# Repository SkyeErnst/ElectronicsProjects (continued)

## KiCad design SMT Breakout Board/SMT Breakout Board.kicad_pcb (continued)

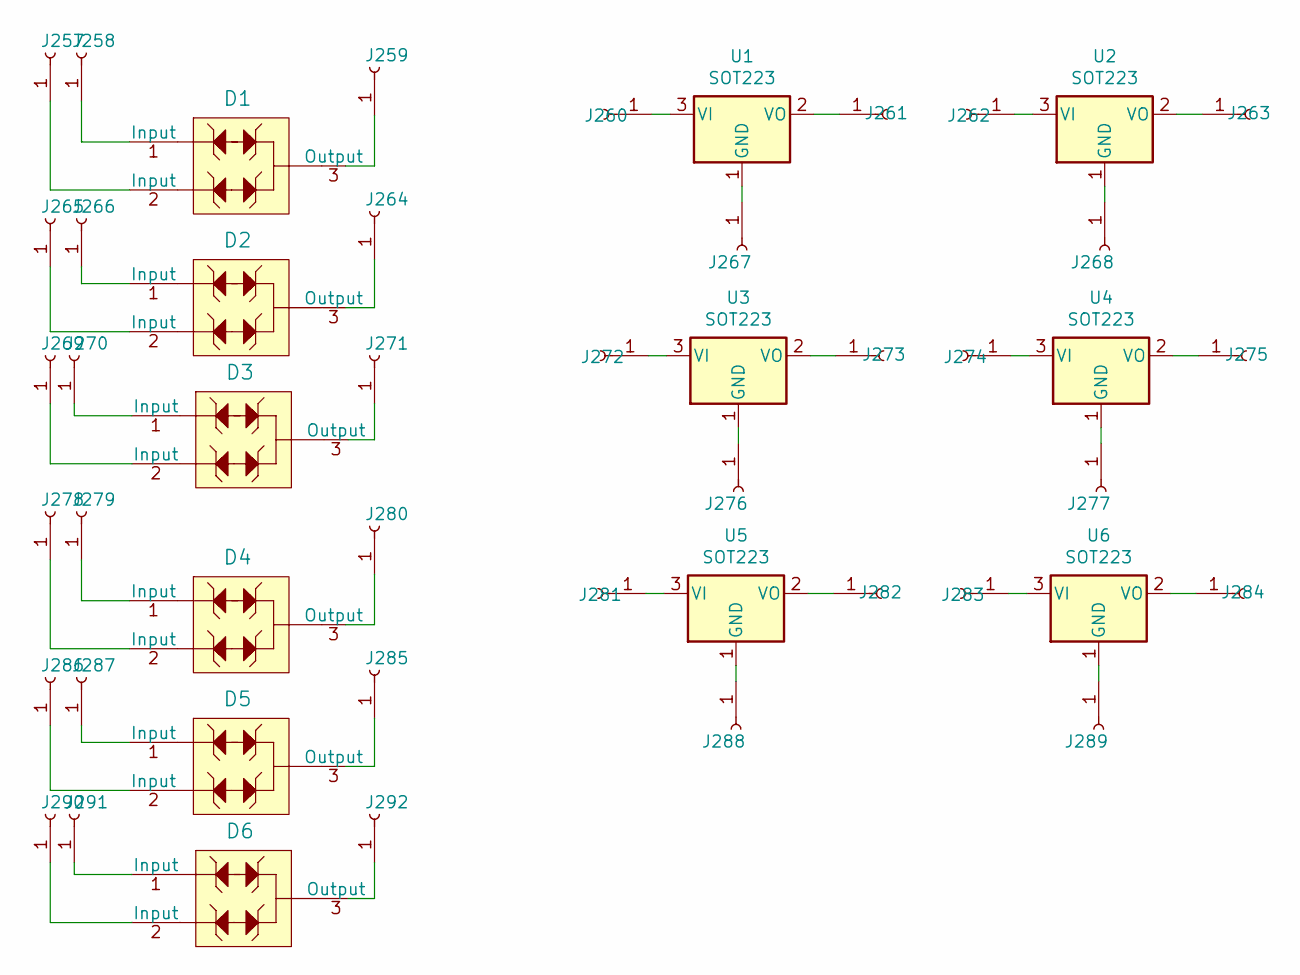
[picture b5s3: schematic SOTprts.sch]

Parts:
D1, D2, D3, D4, D5, D6: CDSOT23-SM712; SOT-23-3; MPN CDSOT23-SM712; Digi-Key_PN CDSOT23-SM712CT-ND
J257, J258, J259, J260, J261, J262, J263, J264, J265, J266, J267, J268, J269, J270, J271, J272, J273, J274, J275, J276, J277, J278, J279, J280, J281, J282, J283, J284, J285, J286, J287, J288, J289, J290, J291, J292: Conn_01x01_Female; PinSocket_1x01_P2.00mm_Vertical
U1, U2, U3, U4, U5, U6: SOT223; SOT-223-3_TabPin2

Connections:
unnamed: D1.1 (Input), J258.1
unnamed: D1.2 (Input), J257.1
unnamed: D1.3 (Output), J259.1
unnamed: D2.1 (Input), J266.1
unnamed: D2.2 (Input), J265.1
unnamed: D2.3 (Output), J264.1
unnamed: D3.1 (Input), J270.1
unnamed: D3.2 (Input), J269.1
unnamed: D3.3 (Output), J271.1
unnamed: D4.1 (Input), J279.1
unnamed: D4.2 (Input), J278.1
unnamed: D4.3 (Output), J280.1
unnamed: D5.1 (Input), J287.1
unnamed: D5.2 (Input), J286.1
unnamed: D5.3 (Output), J285.1
unnamed: D6.1 (Input), J291.1
unnamed: D6.2 (Input), J290.1
unnamed: D6.3 (Output), J292.1
unnamed: J260.1, U1.3 (VI)
unnamed: J261.1, U1.2 (VO)
unnamed: J262.1, U2.3 (VI)
unnamed: J263.1, U2.2 (VO)
unnamed: J267.1, U1.1 (GND)
unnamed: J268.1, U2.1 (GND)
unnamed: J272.1, U3.3 (VI)
unnamed: J273.1, U3.2 (VO)
unnamed: J274.1, U4.3 (VI)
unnamed: J275.1, U4.2 (VO)
unnamed: J276.1, U3.1 (GND)
unnamed: J277.1, U4.1 (GND)
unnamed: J281.1, U5.3 (VI)
unnamed: J282.1, U5.2 (VO)
unnamed: J283.1, U6.3 (VI)
unnamed: J284.1, U6.2 (VO)
unnamed: J288.1, U5.1 (GND)
unnamed: J289.1, U6.1 (GND)

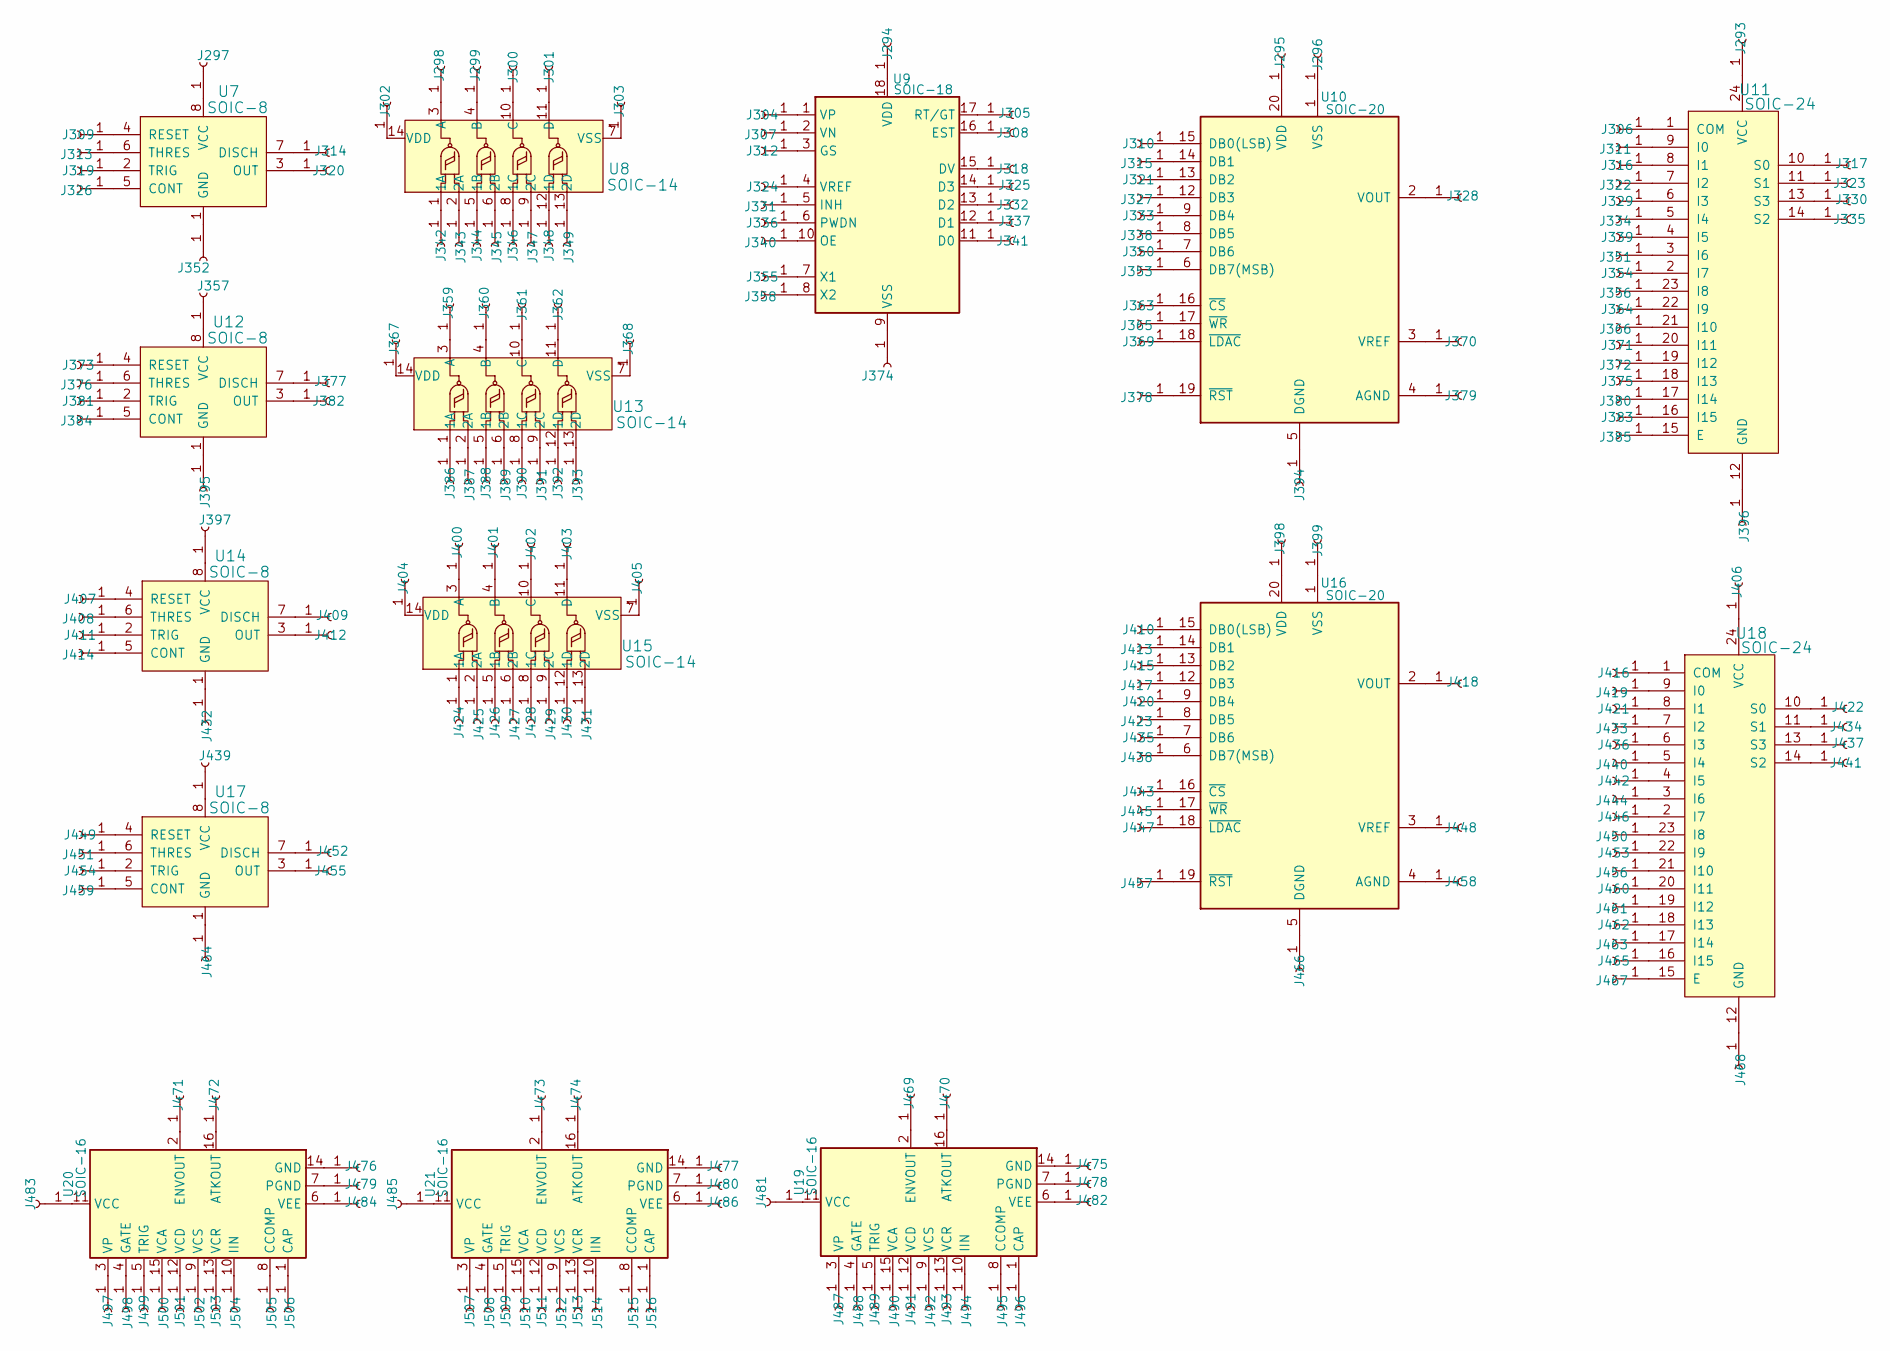
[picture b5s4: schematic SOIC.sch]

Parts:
J293, J294, J295, J296, J297, J298, J299, J300, J301, J302, J303, J304, J305, J306, J307, J308, J309, J310, J311, J312, J313, J314, J315, J316, J317, J318, J319, J320, J321, J322, J323, J324, J325, J326, J327, J328, J329, J330, J331, J332, J333, J334, J335, J336, J337, J338, J339, J340, J341, J342, J343, J344, J345, J346, J347, J348, J349, J350, J351, J352, J353, J354, J355, J356, J357, J358, J359, J360, J361, J362, J363, J364, J365, J366, J367, J368, J369, J370, J371, J372, J373, J374, J375, J376, J377, J378, J379, J380, J381, J382, J383, J384, J385, J386, J387, J388, J389, J390, J391, J392, J393, J394, J395, J396, J397, J398, J399, J400, J401, J402, J403, J404, J405, J406, J407, J408, J409, J410, J411, J412, J413, J414, J415, J416, J417, J418, J419, J420, J421, J422, J423, J424, J425, J426, J427, J428, J429, J430, J431, J432, J433, J434, J435, J436, J437, J438, J439, J440, J441, J442, J443, J444, J445, J446, J447, J448, J449, J450, J451, J452, J453, J454, J455, J456, J457, J458, J459, J460, J461, J462, J463, J464, J465, J466, J467, J468, J469, J470, J471, J472, J473, J474, J475, J476, J477, J478, J479, J480, J481, J482, J483, J484, J485, J486, J487, J488, J489, J490, J491, J492, J493, J494, J495, J496, J497, J498, J499, J500, J501, J502, J503, J504, J505, J506, J507, J508, J509, J510, J511, J512, J513, J514, J515, J516: Conn_01x01_Female; PinSocket_1x01_P2.00mm_Vertical
U7, U12, U14, U17: SOIC-8; SOIC-8_W3.9mm; MPN NE555DR; Digi-Key_PN 296-6501-1-ND
U8, U13, U15: SOIC-14; SOIC-14_W3.9mm; MPN MC14093BDR2G; Digi-Key_PN MC14093BDR2GOSCT-ND
U9: SOIC-18; SOIC-18W_7.5x11.6mm_P1.27mm
U10, U16: SOIC-20; SOIC-20W_7.5x12.8mm_P1.27mm
U11, U18: SOIC-24; SOIC-24_W7.50mm; MPN CD74HC4067M96; Digi-Key_PN 296-29408-1-ND
U19, U20, U21: SOIC-16; SOIC-16_3.9x9.9mm_P1.27mm

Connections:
unnamed: J293.1, U11.24 (VCC)
unnamed: J294.1, U9.18 (VDD)
unnamed: J295.1, U10.20 (VDD)
unnamed: J296.1, U10.1 (VSS)
unnamed: J297.1, U7.8 (VCC)
unnamed: J298.1, U8.3 (A)
unnamed: J299.1, U8.4 (B)
unnamed: J300.1, U8.10 (C)
unnamed: J301.1, U8.11 (D)
unnamed: J302.1, U8.14 (VDD)
unnamed: J303.1, U8.7 (VSS)
unnamed: J304.1, U9.1 (VP)
unnamed: J305.1, U9.17 (RT/GT)
unnamed: J306.1, U11.1 (COM)
unnamed: J307.1, U9.2 (VN)
unnamed: J308.1, U9.16 (EST)
unnamed: J309.1, U7.4 (RESET)
unnamed: J310.1, U10.15 (DB0(LSB))
unnamed: J311.1, U11.9 (I0)
unnamed: J312.1, U9.3 (GS)
unnamed: J313.1, U7.6 (THRES)
unnamed: J314.1, U7.7 (DISCH)
unnamed: J315.1, U10.14 (DB1)
unnamed: J316.1, U11.8 (I1)
unnamed: J317.1, U11.10 (S0)
unnamed: J318.1, U9.15 (DV)
unnamed: J319.1, U7.2 (TRIG)
unnamed: J320.1, U7.3 (OUT)
unnamed: J321.1, U10.13 (DB2)
unnamed: J322.1, U11.7 (I2)
unnamed: J323.1, U11.11 (S1)
unnamed: J324.1, U9.4 (VREF)
unnamed: J325.1, U9.14 (D3)
unnamed: J326.1, U7.5 (CONT)
unnamed: J327.1, U10.12 (DB3)
unnamed: J328.1, U10.2 (VOUT)
unnamed: J329.1, U11.6 (I3)
unnamed: J330.1, U11.13 (S3)
unnamed: J331.1, U9.5 (INH)
unnamed: J332.1, U9.13 (D2)
unnamed: J333.1, U10.9 (DB4)
unnamed: J334.1, U11.5 (I4)
unnamed: J335.1, U11.14 (S2)
unnamed: J336.1, U9.6 (PWDN)
unnamed: J337.1, U9.12 (D1)
unnamed: J338.1, U10.8 (DB5)
unnamed: J339.1, U11.4 (I5)
unnamed: J340.1, U9.10 (OE)
unnamed: J341.1, U9.11 (D0)
unnamed: J342.1, U8.1 (1A)
unnamed: J343.1, U8.2 (2A)
unnamed: J344.1, U8.5 (1B)
unnamed: J345.1, U8.6 (2B)
unnamed: J346.1, U8.8 (1C)
unnamed: J347.1, U8.9 (2C)
unnamed: J348.1, U8.12 (1D)
unnamed: J349.1, U8.13 (2D)
unnamed: J350.1, U10.7 (DB6)
unnamed: J351.1, U11.3 (I6)
unnamed: J352.1, U7.1 (GND)
unnamed: J353.1, U10.6 (DB7(MSB))
unnamed: J354.1, U11.2 (I7)
unnamed: J355.1, U9.7 (X1)
unnamed: J356.1, U11.23 (I8)
unnamed: J357.1, U12.8 (VCC)
unnamed: J358.1, U9.8 (X2)
unnamed: J359.1, U13.3 (A)
unnamed: J360.1, U13.4 (B)
unnamed: J361.1, U13.10 (C)
unnamed: J362.1, U13.11 (D)
unnamed: J363.1, U10.16 (~CS)
unnamed: J364.1, U11.22 (I9)
unnamed: J365.1, U10.17 (~WR)
unnamed: J366.1, U11.21 (I10)
unnamed: J367.1, U13.14 (VDD)
unnamed: J368.1, U13.7 (VSS)
unnamed: J369.1, U10.18 (~LDAC)
unnamed: J370.1, U10.3 (VREF)
unnamed: J371.1, U11.20 (I11)
unnamed: J372.1, U11.19 (I12)
unnamed: J373.1, U12.4 (RESET)
unnamed: J374.1, U9.9 (VSS)
unnamed: J375.1, U11.18 (I13)
unnamed: J376.1, U12.6 (THRES)
unnamed: J377.1, U12.7 (DISCH)
unnamed: J378.1, U10.19 (~RST)
unnamed: J379.1, U10.4 (AGND)
unnamed: J380.1, U11.17 (I14)
unnamed: J381.1, U12.2 (TRIG)
unnamed: J382.1, U12.3 (OUT)
unnamed: J383.1, U11.16 (I15)
unnamed: J384.1, U12.5 (CONT)
unnamed: J385.1, U11.15 (E)
unnamed: J386.1, U13.1 (1A)
unnamed: J387.1, U13.2 (2A)
unnamed: J388.1, U13.5 (1B)
unnamed: J389.1, U13.6 (2B)
unnamed: J390.1, U13.8 (1C)
unnamed: J391.1, U13.9 (2C)
unnamed: J392.1, U13.12 (1D)
unnamed: J393.1, U13.13 (2D)
unnamed: J394.1, U10.5 (DGND)
unnamed: J395.1, U12.1 (GND)
unnamed: J396.1, U11.12 (GND)
unnamed: J397.1, U14.8 (VCC)
unnamed: J398.1, U16.20 (VDD)
unnamed: J399.1, U16.1 (VSS)
unnamed: J400.1, U15.3 (A)
unnamed: J401.1, U15.4 (B)
unnamed: J402.1, U15.10 (C)
unnamed: J403.1, U15.11 (D)
unnamed: J404.1, U15.14 (VDD)
unnamed: J405.1, U15.7 (VSS)
unnamed: J406.1, U18.24 (VCC)
unnamed: J407.1, U14.4 (RESET)
unnamed: J408.1, U14.6 (THRES)
unnamed: J409.1, U14.7 (DISCH)
unnamed: J410.1, U16.15 (DB0(LSB))
unnamed: J411.1, U14.2 (TRIG)
unnamed: J412.1, U14.3 (OUT)
unnamed: J413.1, U16.14 (DB1)
unnamed: J414.1, U14.5 (CONT)
unnamed: J415.1, U16.13 (DB2)
unnamed: J416.1, U18.1 (COM)
unnamed: J417.1, U16.12 (DB3)
unnamed: J418.1, U16.2 (VOUT)
unnamed: J419.1, U18.9 (I0)
unnamed: J420.1, U16.9 (DB4)
unnamed: J421.1, U18.8 (I1)
unnamed: J422.1, U18.10 (S0)
unnamed: J423.1, U16.8 (DB5)
unnamed: J424.1, U15.1 (1A)
unnamed: J425.1, U15.2 (2A)
unnamed: J426.1, U15.5 (1B)
unnamed: J427.1, U15.6 (2B)
unnamed: J428.1, U15.8 (1C)
unnamed: J429.1, U15.9 (2C)
unnamed: J430.1, U15.12 (1D)
unnamed: J431.1, U15.13 (2D)
unnamed: J432.1, U14.1 (GND)
unnamed: J433.1, U18.7 (I2)
unnamed: J434.1, U18.11 (S1)
unnamed: J435.1, U16.7 (DB6)
unnamed: J436.1, U18.6 (I3)
unnamed: J437.1, U18.13 (S3)
unnamed: J438.1, U16.6 (DB7(MSB))
unnamed: J439.1, U17.8 (VCC)
unnamed: J440.1, U18.5 (I4)
unnamed: J441.1, U18.14 (S2)
unnamed: J442.1, U18.4 (I5)
unnamed: J443.1, U16.16 (~CS)
unnamed: J444.1, U18.3 (I6)
unnamed: J445.1, U16.17 (~WR)
unnamed: J446.1, U18.2 (I7)
unnamed: J447.1, U16.18 (~LDAC)
unnamed: J448.1, U16.3 (VREF)
unnamed: J449.1, U17.4 (RESET)
unnamed: J450.1, U18.23 (I8)
unnamed: J451.1, U17.6 (THRES)
unnamed: J452.1, U17.7 (DISCH)
unnamed: J453.1, U18.22 (I9)
unnamed: J454.1, U17.2 (TRIG)
unnamed: J455.1, U17.3 (OUT)
unnamed: J456.1, U18.21 (I10)
unnamed: J457.1, U16.19 (~RST)
unnamed: J458.1, U16.4 (AGND)
unnamed: J459.1, U17.5 (CONT)
unnamed: J460.1, U18.20 (I11)
unnamed: J461.1, U18.19 (I12)
unnamed: J462.1, U18.18 (I13)
unnamed: J463.1, U18.17 (I14)
unnamed: J464.1, U17.1 (GND)
unnamed: J465.1, U18.16 (I15)
unnamed: J466.1, U16.5 (DGND)
unnamed: J467.1, U18.15 (E)
unnamed: J468.1, U18.12 (GND)
unnamed: J469.1, U19.2 (ENVOUT)
unnamed: J470.1, U19.16 (ATKOUT)
unnamed: J471.1, U20.2 (ENVOUT)
unnamed: J472.1, U20.16 (ATKOUT)
unnamed: J473.1, U21.2 (ENVOUT)
unnamed: J474.1, U21.16 (ATKOUT)
unnamed: J475.1, U19.14 (GND)
unnamed: J476.1, U20.14 (GND)
unnamed: J477.1, U21.14 (GND)
unnamed: J478.1, U19.7 (PGND)
unnamed: J479.1, U20.7 (PGND)
unnamed: J480.1, U21.7 (PGND)
unnamed: J481.1, U19.11 (VCC)
unnamed: J482.1, U19.6 (VEE)
unnamed: J483.1, U20.11 (VCC)
unnamed: J484.1, U20.6 (VEE)
unnamed: J485.1, U21.11 (VCC)
unnamed: J486.1, U21.6 (VEE)
unnamed: J487.1, U19.3 (VP)
unnamed: J488.1, U19.4 (GATE)
unnamed: J489.1, U19.5 (TRIG)
unnamed: J490.1, U19.15 (VCA)
unnamed: J491.1, U19.12 (VCD)
unnamed: J492.1, U19.9 (VCS)
unnamed: J493.1, U19.13 (VCR)
unnamed: J494.1, U19.10 (IIN)
unnamed: J495.1, U19.8 (CCOMP)
unnamed: J496.1, U19.1 (CAP)
unnamed: J497.1, U20.3 (VP)
unnamed: J498.1, U20.4 (GATE)
unnamed: J499.1, U20.5 (TRIG)
unnamed: J500.1, U20.15 (VCA)
unnamed: J501.1, U20.12 (VCD)
unnamed: J502.1, U20.9 (VCS)
unnamed: J503.1, U20.13 (VCR)
unnamed: J504.1, U20.10 (IIN)
unnamed: J505.1, U20.8 (CCOMP)
unnamed: J506.1, U20.1 (CAP)
unnamed: J507.1, U21.3 (VP)
unnamed: J508.1, U21.4 (GATE)
unnamed: J509.1, U21.5 (TRIG)
unnamed: J510.1, U21.15 (VCA)
unnamed: J511.1, U21.12 (VCD)
unnamed: J512.1, U21.9 (VCS)
unnamed: J513.1, U21.13 (VCR)
unnamed: J514.1, U21.10 (IIN)
unnamed: J515.1, U21.8 (CCOMP)
unnamed: J516.1, U21.1 (CAP)

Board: 2 copper layers, 623 parts (0 on the bottom side), 455 nets, no tracks yet.

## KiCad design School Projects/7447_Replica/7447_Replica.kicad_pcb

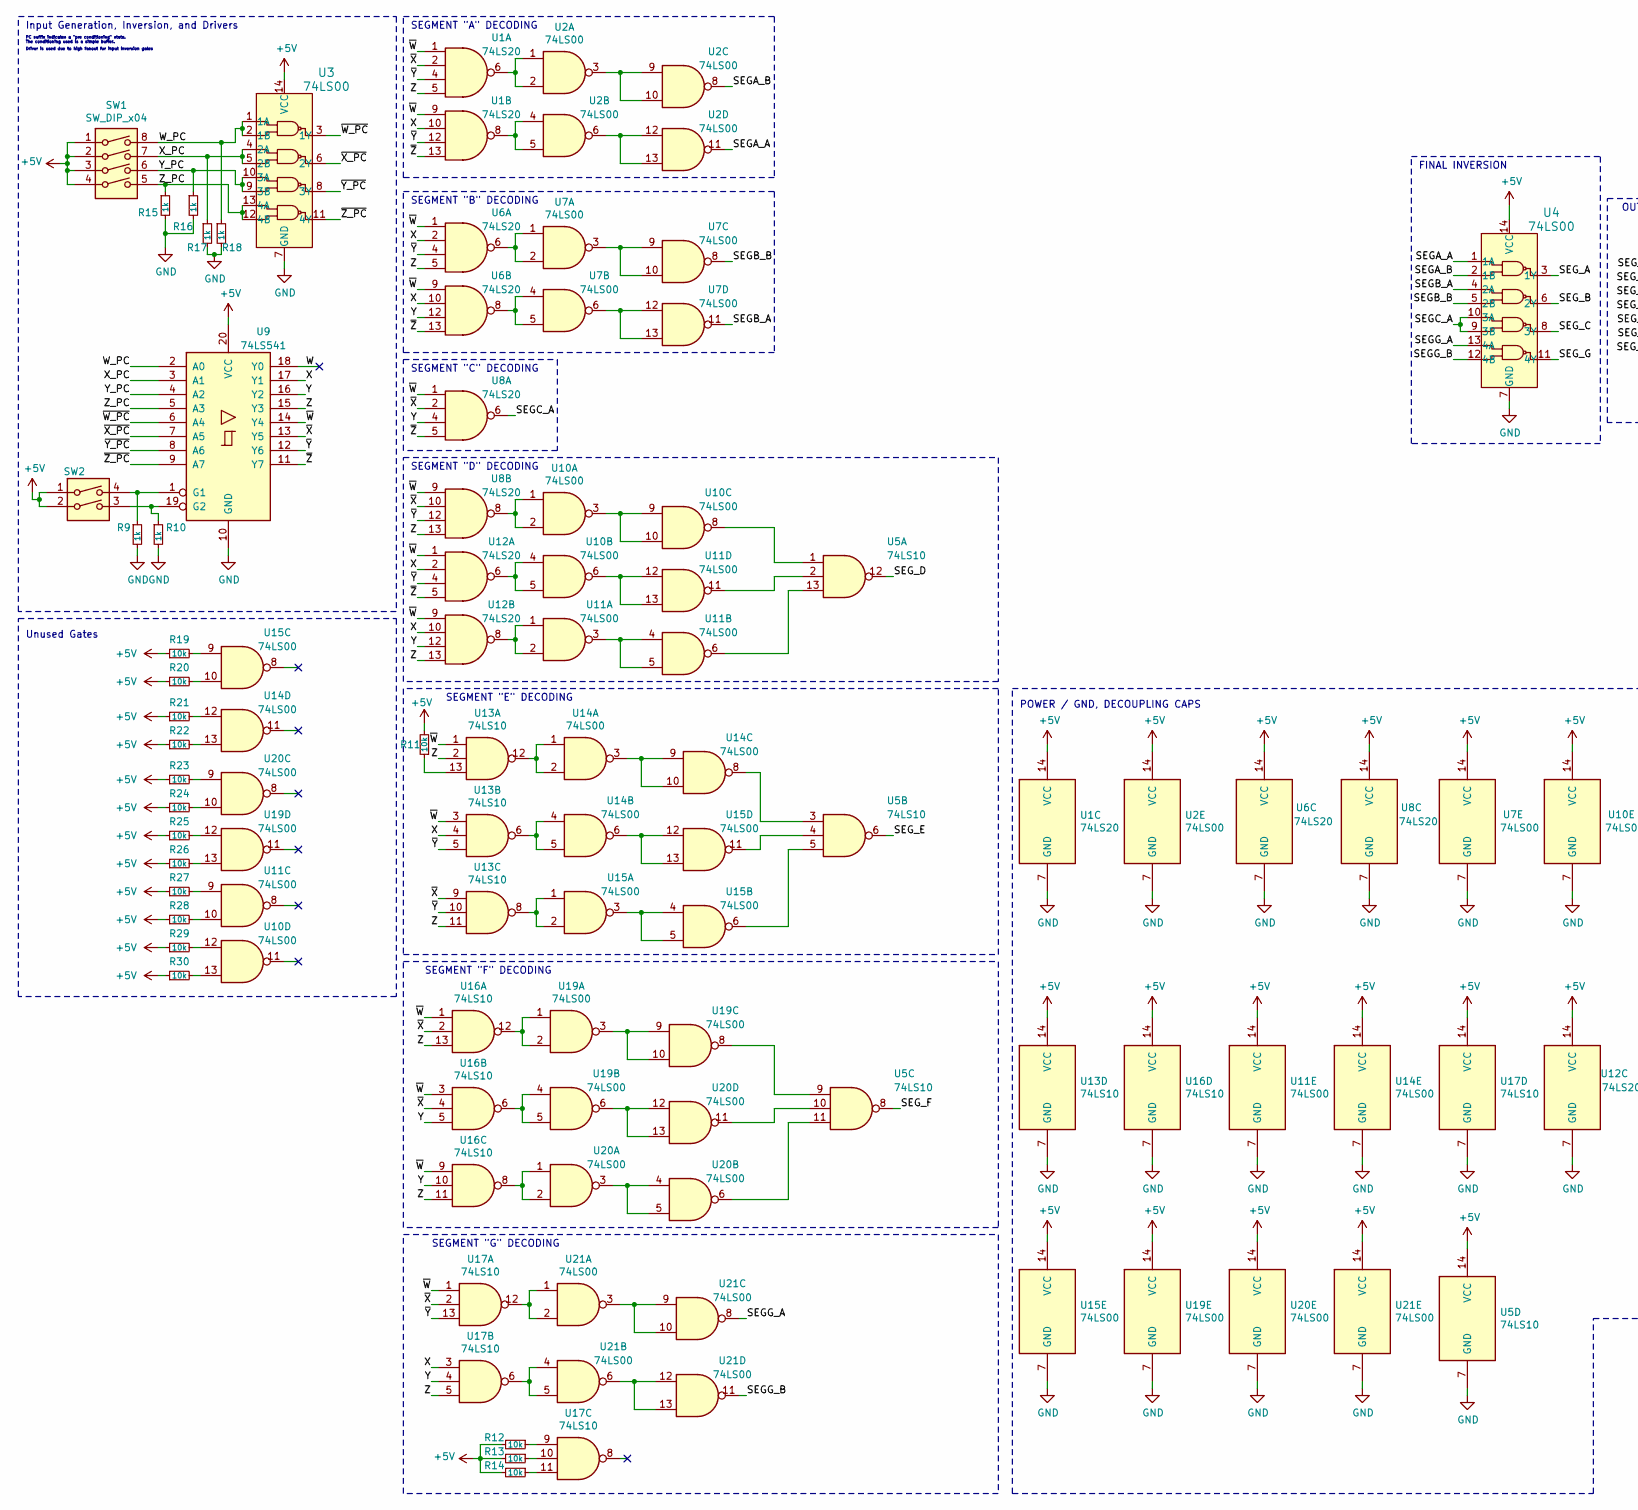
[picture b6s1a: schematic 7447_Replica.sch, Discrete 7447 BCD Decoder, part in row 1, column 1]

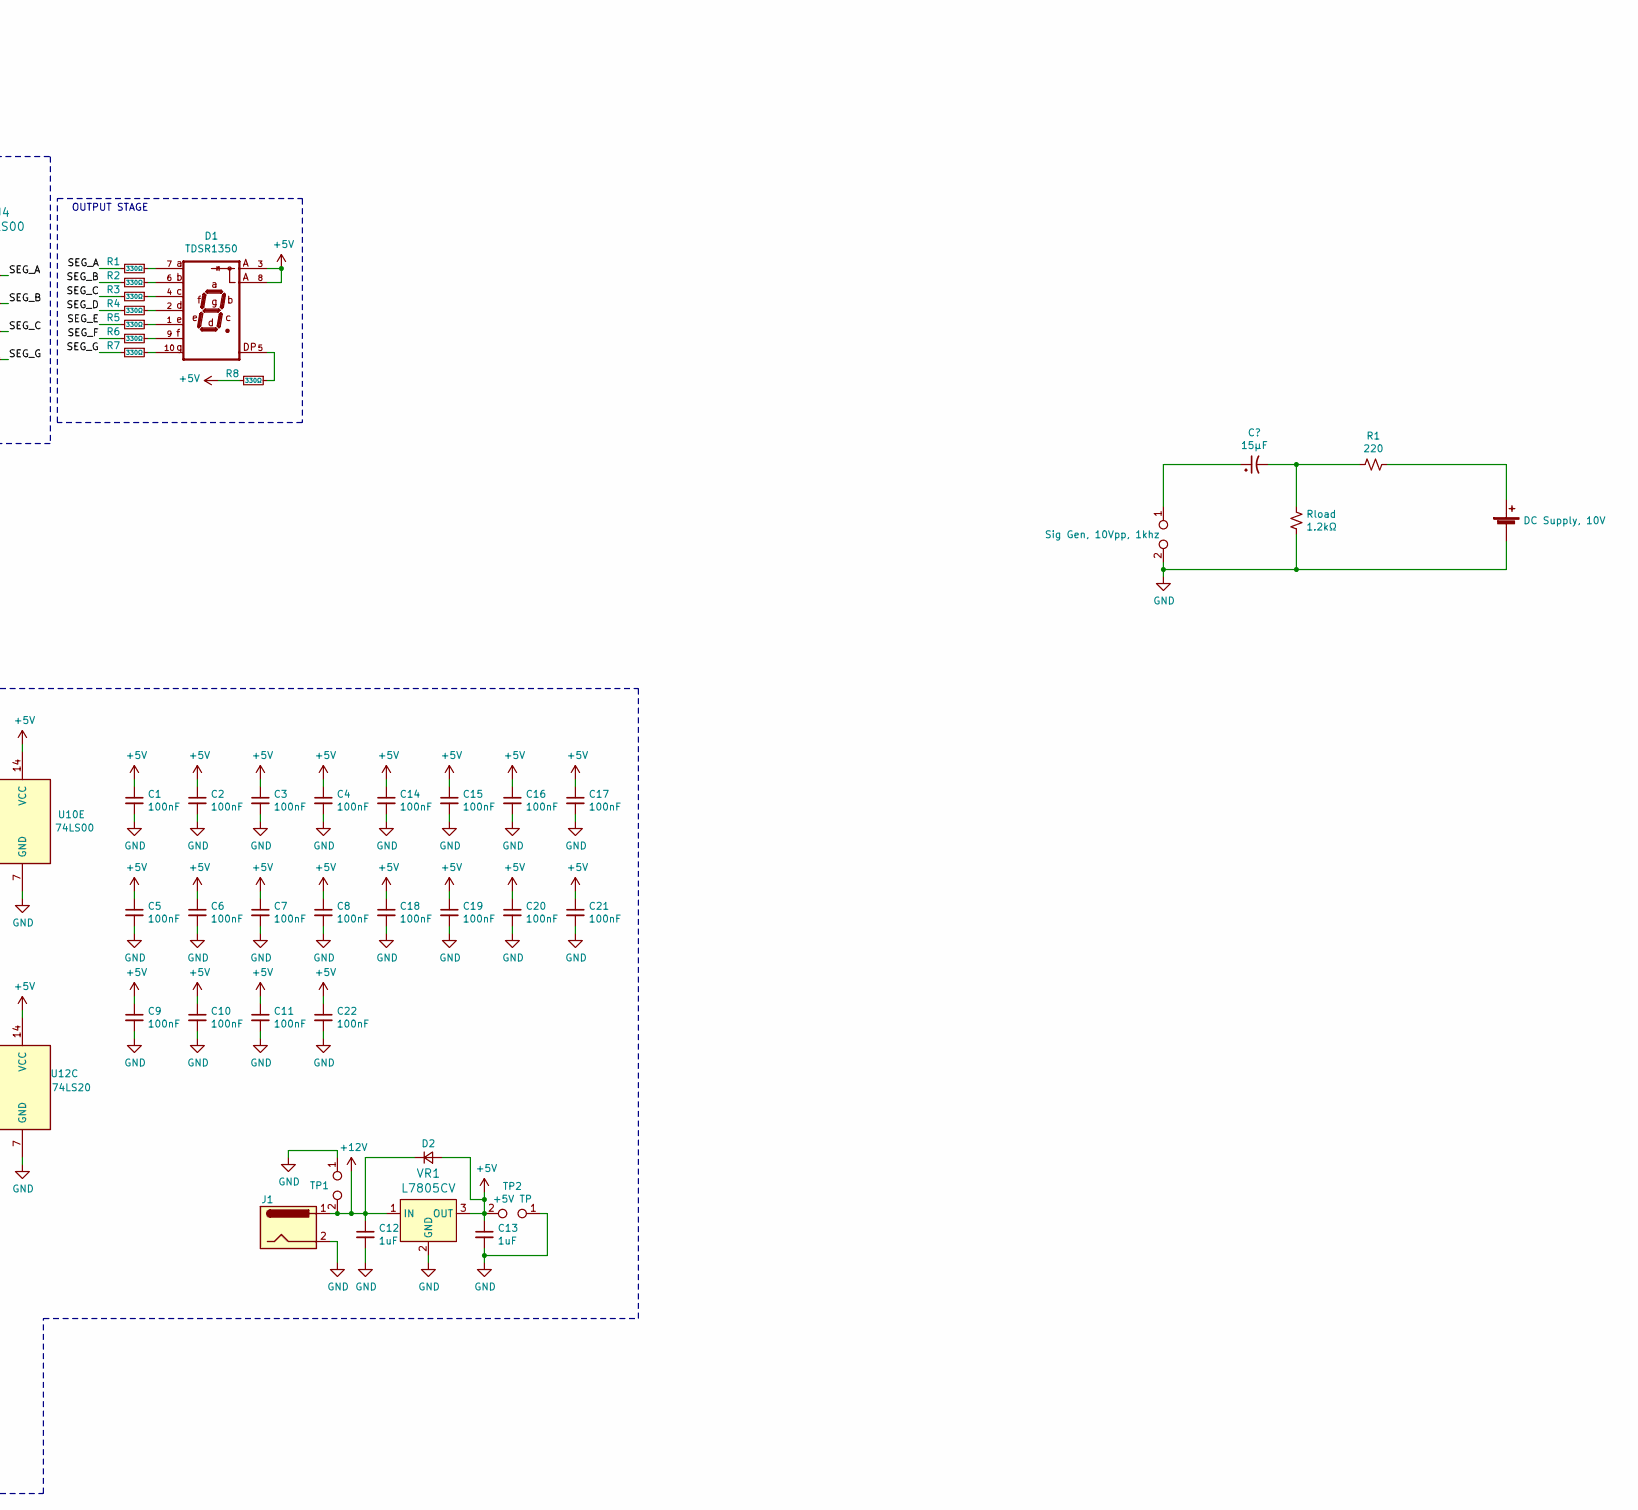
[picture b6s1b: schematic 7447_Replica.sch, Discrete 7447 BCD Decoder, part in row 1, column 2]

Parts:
C1, C2, C3, C4, C5, C6, C7, C8, C9, C10, C11, C14, C15, C16, C17, C18, C19, C20, C21, C22: 100nF; C_0805_2012Metric_Pad1.15x1.40mm_HandSolder
C12, C13: 1uF; C_0805_2012Metric_Pad1.15x1.40mm_HandSolder
D1: TDSR1350; DIPS1524W50P254L1240H710Q10; PARTREV 1.3
D2: D_Small; D_A-405_P10.16mm_Horizontal
J1: Barrel_Jack; BarrelJack_CUI_PJ-063AH_Horizontal
R1, R2, R3, R4, R5, R6, R7, R8: 330Ω; R_0805_2012Metric_Pad1.15x1.40mm_HandSolder
R9, R10, R15, R16, R17, R18: 1k; R_0805_2012Metric_Pad1.15x1.40mm_HandSolder
R11, R12, R13, R14, R19, R20, R21, R22, R23, R24, R25, R26, R27, R28, R29, R30: 10k; R_0805_2012Metric_Pad1.15x1.40mm_HandSolder
Rload: 1.2kΩ
SW1: SW_DIP_x04; SW_DIP_SPSTx04_Slide_6.7x11.72mm_W7.62mm_P2.54mm_LowProfile
SW2: SW_DIP_x02; SW_DIP_SPSTx02_Slide_6.7x6.64mm_W7.62mm_P2.54mm_LowProfile
TP1: 12V TP; TestPoint_2Pads_Pitch5.08mm_Drill1.3mm
TP2: +5V TP; TestPoint_2Pads_Pitch5.08mm_Drill1.3mm
U1, U6, U8, U12: 74LS20; SOIC-14_3.9x8.7mm_P1.27mm
U2, U7, U10, U11, U14, U15, U19, U20, U21: 74LS00; SOIC-14_3.9x8.7mm_P1.27mm
U3, U4: 74LS00; SOIC-14_3.9x8.7mm_P1.27mm; MPN SN74LS00N; Digi-Key_PN 296-1626-ND
U5, U13, U16, U17: 74LS10; SOIC-14_3.9x8.7mm_P1.27mm
U9: 74LS541; DIP-20_W7.62mm_LongPads
VR1: L7805CV; TO-220-3_Vertical; MPN L7805CV; Digi-Key_PN 497-1443-5-ND

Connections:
+5V: C1.1, C2.1, C3.1, C4.1, C5.1, C6.1, C7.1, C8.1, C9.1, C10.1, C11.1, C13.1, C14.1, C15.1, C16.1, C17.1, C18.1, C19.1, C20.1, C21.1, C22.1, D1.3, D1.8, D2.2 (A), R8.2, R11.2, R12.2, R13.2, R14.2, R19.1, R20.1, R21.1, R22.1, R23.1, R24.1, R25.1, R26.1, R27.1, R28.1, R29.1, R30.1, SW1.1, SW1.2, SW1.3, SW1.4, SW2.1, SW2.2, TP2.2, U1.14 (VCC), U2.14 (VCC), U3.14 (VCC), U4.14 (VCC), U5.14 (VCC), U6.14 (VCC), U7.14 (VCC), U8.14 (VCC), U9.20 (VCC), U10.14 (VCC), U11.14 (VCC), U12.14 (VCC), U13.14 (VCC), U14.14 (VCC), U15.14 (VCC), U16.14 (VCC), U17.14 (VCC), U19.14 (VCC), U20.14 (VCC), U21.14 (VCC), VR1.3 (OUT)
+12V: C12.1, D2.1 (K), J1.1, TP1.2, VR1.1 (IN)
/SEGA_A: U2.11, U4.1 (1A)
/SEGA_B: U2.8, U4.2 (1B)
/SEGB_A: U4.4 (2A), U7.11
/SEGB_B: U4.5 (2B), U7.8
/SEGC_A: U4.9 (3B), U4.10 (3A), U8.6
/SEGG_A: U4.13 (4A), U21.8
/SEGG_B: U4.12 (4B), U21.11
/SEG_A: R1.2, U4.3 (1Y)
/SEG_B: R2.2, U4.6 (2Y)
/SEG_C: R3.2, U4.8 (3Y)
/SEG_D: R4.2, U5.12
/SEG_E: R5.2, U5.6
/SEG_F: R6.2, U5.8
/SEG_G: R7.2, U4.11 (4Y)
/W: U9.18 (Y0)
/W_PC: R18.1, SW1.8, U3.1 (1A), U3.2 (1B), U9.2 (A0)
/X: U1.10, U6.2, U6.10, U9.17 (Y1), U12.2, U12.10, U13.4, U17.3
/X_PC: R17.1, SW1.7, U3.4 (2A), U3.5 (2B), U9.3 (A1)
/Y: U6.12, U8.4, U9.16 (Y2), U12.12, U16.5, U16.10, U17.4
/Y_PC: R16.1, SW1.6, U3.9 (3B), U3.10 (3A), U9.4 (A2)
/Z: U1.5, U6.5, U8.13, U9.15 (Y3), U12.13, U13.2, U13.11, U16.11, U16.13, U17.5
/Z_PC: R15.1, SW1.5, U3.12 (4B), U3.13 (4A), U9.5 (A3)
/~W: U1.1, U1.9, U6.1, U6.9, U8.1, U8.9, U9.14 (Y4), U12.1, U12.9, U13.1, U13.3, U16.1, U16.3, U16.9, U17.1
/~W_PC: U3.3 (1Y), U9.6 (A4)
/~X: U1.2, U8.2, U8.10, U9.13 (Y5), U13.9, U16.2, U16.4, U17.2
/~X_PC: U3.6 (2Y), U9.7 (A5)
/~Y: U1.4, U1.12, U6.4, U8.12, U9.12 (Y6), U12.4, U13.5, U13.10, U17.13
/~Y_PC: U3.8 (3Y), U9.8 (A6)
/~Z: U1.13, U6.13, U8.5, U9.11 (Y7), U12.5
/~Z_PC: U3.11 (4Y), U9.9 (A7)
GND: C1.2, C2.2, C3.2, C4.2, C5.2, C6.2, C7.2, C8.2, C9.2, C10.2, C11.2, C12.2, C13.2, C14.2, C15.2, C16.2, C17.2, C18.2, C19.2, C20.2, C21.2, C22.2, J1.2, R9.2, R10.2, R15.2, R16.2, R17.2, R18.2, Rload.2, TP1.1, TP2.1, U1.7 (GND), U2.7 (GND), U3.7 (GND), U4.7 (GND), U5.7 (GND), U6.7 (GND), U7.7 (GND), U8.7 (GND), U9.10 (GND), U10.7 (GND), U11.7 (GND), U12.7 (GND), U13.7 (GND), U14.7 (GND), U15.7 (GND), U16.7 (GND), U17.7 (GND), U19.7 (GND), U20.7 (GND), U21.7 (GND), VR1.2 (GND)
unnamed: D1.1, R5.1
unnamed: D1.2, R4.1
unnamed: D1.4, R3.1
unnamed: D1.5, R8.1
unnamed: D1.6, R2.1
unnamed: D1.7, R1.1, Rload.1
unnamed: D1.9, R6.1
unnamed: D1.10, R7.1
unnamed: R9.1, SW2.4, U9.1 (G1)
unnamed: R10.1, SW2.3, U9.19 (G2)
unnamed: R11.1, U13.13
unnamed: R12.1, U17.9
unnamed: R13.1, U17.10
unnamed: R14.1, U17.11
unnamed: R19.2, U15.9
unnamed: R20.2, U15.10
unnamed: R21.2, U14.12
unnamed: R22.2, U14.13
unnamed: R23.2, U20.9
unnamed: R24.2, U20.10
unnamed: R25.2, U19.12
unnamed: R26.2, U19.13
unnamed: R27.2, U11.9
unnamed: R28.2, U11.10
unnamed: R29.2, U10.12
unnamed: R30.2, U10.13
unnamed: U1.6, U2.1, U2.2
unnamed: U1.8, U2.4, U2.5
unnamed: U2.3, U2.9, U2.10
unnamed: U2.6, U2.12, U2.13
unnamed: U6.6, U7.1, U7.2
unnamed: U6.8, U7.4, U7.5
unnamed: U7.3, U7.9, U7.10
unnamed: U7.6, U7.12, U7.13
unnamed: U8.8, U10.1, U10.2
unnamed: U10.4, U10.5, U12.6
unnamed: U10.6, U11.12, U11.13
unnamed: U5.1, U10.8
unnamed: U10.3, U10.9, U10.10
unnamed: U11.1, U11.2, U12.8
unnamed: U11.3, U11.4, U11.5
unnamed: U5.13, U11.6
unnamed: U5.2, U11.11
unnamed: U13.6, U14.4, U14.5
unnamed: U13.8, U15.1, U15.2
unnamed: U13.12, U14.1, U14.2
unnamed: U14.6, U15.12, U15.13
unnamed: U5.3, U14.8
unnamed: U14.3, U14.9, U14.10
unnamed: U15.3, U15.4, U15.5
unnamed: U5.5, U15.6
unnamed: U5.4, U15.11
unnamed: U16.6, U19.4, U19.5
unnamed: U16.8, U20.1, U20.2
unnamed: U16.12, U19.1, U19.2
unnamed: U17.6, U21.4, U21.5
unnamed: U17.12, U21.1, U21.2
unnamed: U19.6, U20.12, U20.13
unnamed: U5.9, U19.8
unnamed: U19.3, U19.9, U19.10
unnamed: U20.3, U20.4, U20.5
unnamed: U5.11, U20.6
unnamed: U5.10, U20.11
unnamed: U21.3, U21.9, U21.10
unnamed: U21.6, U21.12, U21.13

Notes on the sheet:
Input Generation, Inversion, and Drivers
Driver is used due to high fanout for input inversion gates
PC suffix indicates a "pre conditioning" state. The conditioning used is a simple buffer.
POWER / GND, DECOUPLING CAPS
OUTPUT STAGE
FINAL INVERSION
SEGMENT "G" DECODING
SEGMENT "F" DECODING
SEGMENT "E" DECODING
SEGMENT "D" DECODING
SEGMENT "C" DECODING
SEGMENT "B" DECODING
SEGMENT "A" DECODING
Unused Gates

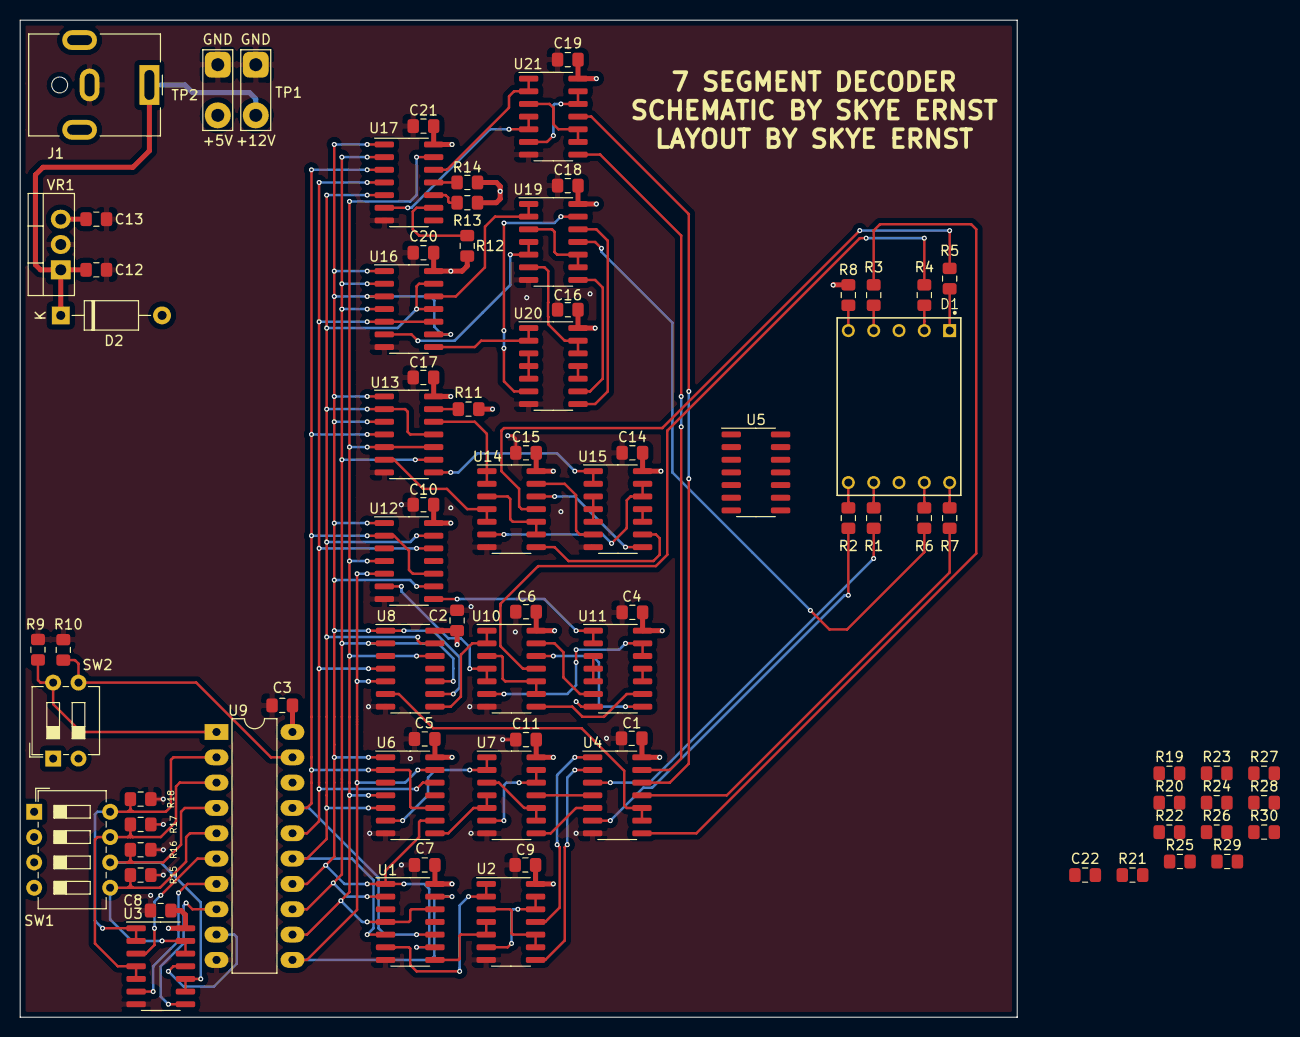
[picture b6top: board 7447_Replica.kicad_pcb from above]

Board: 4 copper layers, 100.0 x 100.0 mm, 80 parts (0 on the bottom side), 97 nets.
